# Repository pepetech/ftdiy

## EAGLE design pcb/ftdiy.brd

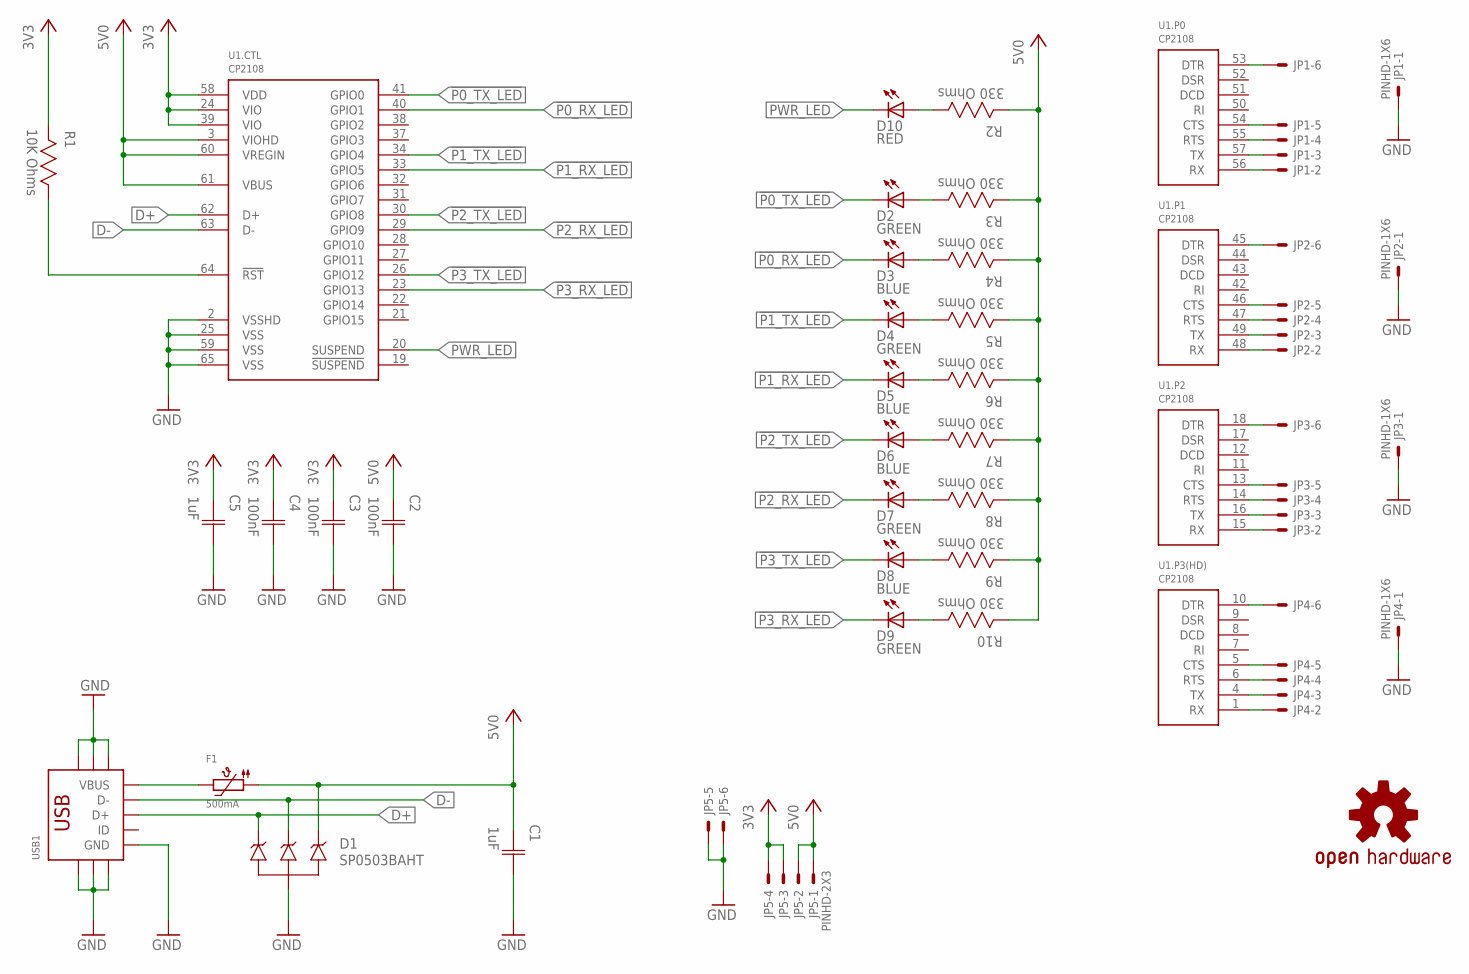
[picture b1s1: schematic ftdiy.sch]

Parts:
C1, C5: 1uF; CAP0603
C2, C3, C4: 100nF; CAP0603
D1: SP0503BAHT; SOT143
D2, D4, D7, D9: GREEN; 0603
D3, D5, D6, D8: BLUE; 0603
D10: RED; 0603
F1: 500mA; 1206
JP1, JP2, JP3, JP4: PINHD-1X6; 1X06
JP5: PINHD-2X3; 2X03
LOGO1: OSHW-LOGOM; OSHW-LOGO-M
R1: 10K Ohms; RES0603
R2, R3, R4, R5, R6, R7, R8, R9, R10: 330 Ohms; RES0603
U1: CP2108; QFN64
USB1: USB-MICRO-B-SMD-FLAT-SIDE

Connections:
3V3: C3.1 (C1), C4.1 (C1), C5.1 (C1), JP5.3, JP5.4, R1.2, U1.24 (VIO), U1.39 (VIO), U1.58 (VDD)
5V0: C1.1 (C1), C2.1 (C1), D1.4, F1.1, JP5.1, JP5.2, R2.2, R3.2, R4.2, R5.2, R6.2, R7.2, R8.2, R9.2, R10.2, U1.3 (VIOHD), U1.60 (VREGIN), U1.61 (VBUS)
!P0_RX_LED: D3.1 (C), U1.40 (GPIO1)
!P0_TX_LED: D2.1 (C), U1.41 (GPIO0)
!P1_RX_LED: D5.1 (C), U1.33 (GPIO5)
!P1_TX_LED: D4.1 (C), U1.34 (GPIO4)
!P2_RX_LED: D7.1 (C), U1.29 (GPIO9)
!P2_TX_LED: D6.1 (C), U1.30 (GPIO8)
!P3_RX_LED: D9.1 (C), U1.23 (GPIO13)
!P3_TX_LED: D8.1 (C), U1.26 (GPIO12)
D+: D1.2, U1.62 (D+), USB1.D+
D-: D1.3, U1.63 (D-), USB1.D-
GND: C1.2 (C2), C2.2 (C2), C3.2 (C2), C4.2 (C2), C5.2 (C2), D1.1, JP1.1, JP2.1, JP3.1, JP4.1, JP5.5, JP5.6, U1.2 (VSSHD), U1.25 (VSS), U1.59 (VSS), U1.65 (VSS), USB1.GND, USB1.SHIELD1 (SHIELD), USB1.SHIELD2 (SHIELD), USB1.SHIELD3 (SHIELD), USB1.SHIELD4 (SHIELD), USB1.SHIELD5 (SHIELD), USB1.SHIELD6 (SHIELD)
unnamed: JP1.2, U1.56 (RX)
unnamed: JP1.3, U1.57 (TX)
unnamed: JP1.4, U1.55 (RTS)
unnamed: JP1.5, U1.54 (CTS)
unnamed: JP1.6, U1.53 (DTR)
unnamed: JP2.2, U1.48 (RX)
unnamed: JP2.3, U1.49 (TX)
unnamed: JP2.4, U1.47 (RTS)
unnamed: JP2.5, U1.46 (CTS)
unnamed: JP2.6, U1.45 (DTR)
unnamed: JP3.2, U1.15 (RX)
unnamed: JP3.3, U1.16 (TX)
unnamed: JP3.4, U1.14 (RTS)
unnamed: JP3.5, U1.13 (CTS)
unnamed: JP3.6, U1.18 (DTR)
unnamed: JP4.2, U1.1 (RX)
unnamed: JP4.3, U1.4 (TX)
unnamed: JP4.4, U1.6 (RTS)
unnamed: JP4.5, U1.5 (CTS)
unnamed: JP4.6, U1.10 (DTR)
unnamed: R1.1, U1.64 (!RST)
unnamed: D10.2 (A), R2.1
unnamed: D2.2 (A), R3.1
unnamed: D3.2 (A), R4.1
unnamed: D4.2 (A), R5.1
unnamed: D5.2 (A), R6.1
unnamed: D6.2 (A), R7.1
unnamed: D7.2 (A), R8.1
unnamed: D8.2 (A), R9.1
unnamed: D9.2 (A), R10.1
unnamed: F1.2, USB1.VBUS
PWR_LED: D10.1 (C), U1.20 (SUSPEND)

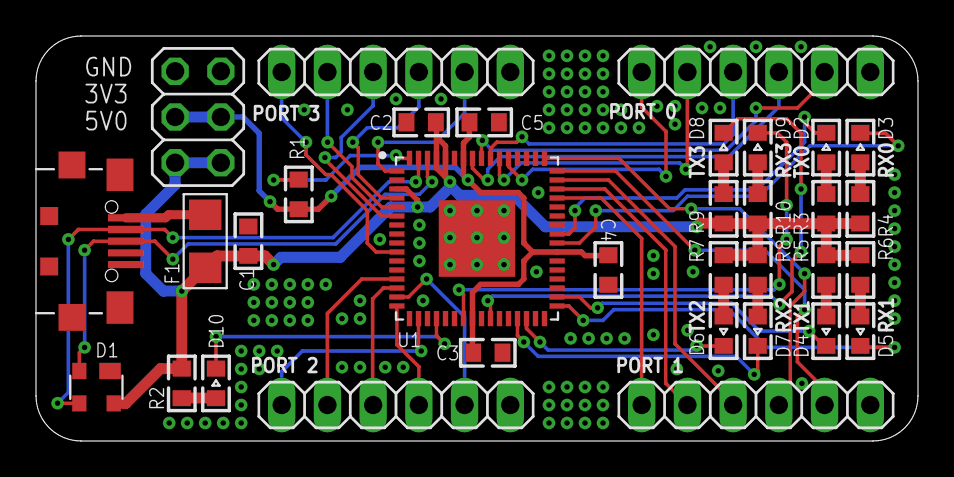
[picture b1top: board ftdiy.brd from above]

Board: 2 copper layers, 49.0 x 22.5 mm, 34 parts (1 on the bottom side), 45 nets.

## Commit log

2019-05-07 Change repository name
2019-05-07 Added eagle project file
2019-05-16 Finish schematic, board and generate gerbers
2019-05-16 DRC check
2019-05-17 Add OSHW logo
2019-05-17 New gerbers
